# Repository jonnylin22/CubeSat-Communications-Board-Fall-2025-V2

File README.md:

# UCI CubeSat Communications Board Version 2 #

Features pinout connector to external MCU  
RX and TX status LEDs  
Organized BOM

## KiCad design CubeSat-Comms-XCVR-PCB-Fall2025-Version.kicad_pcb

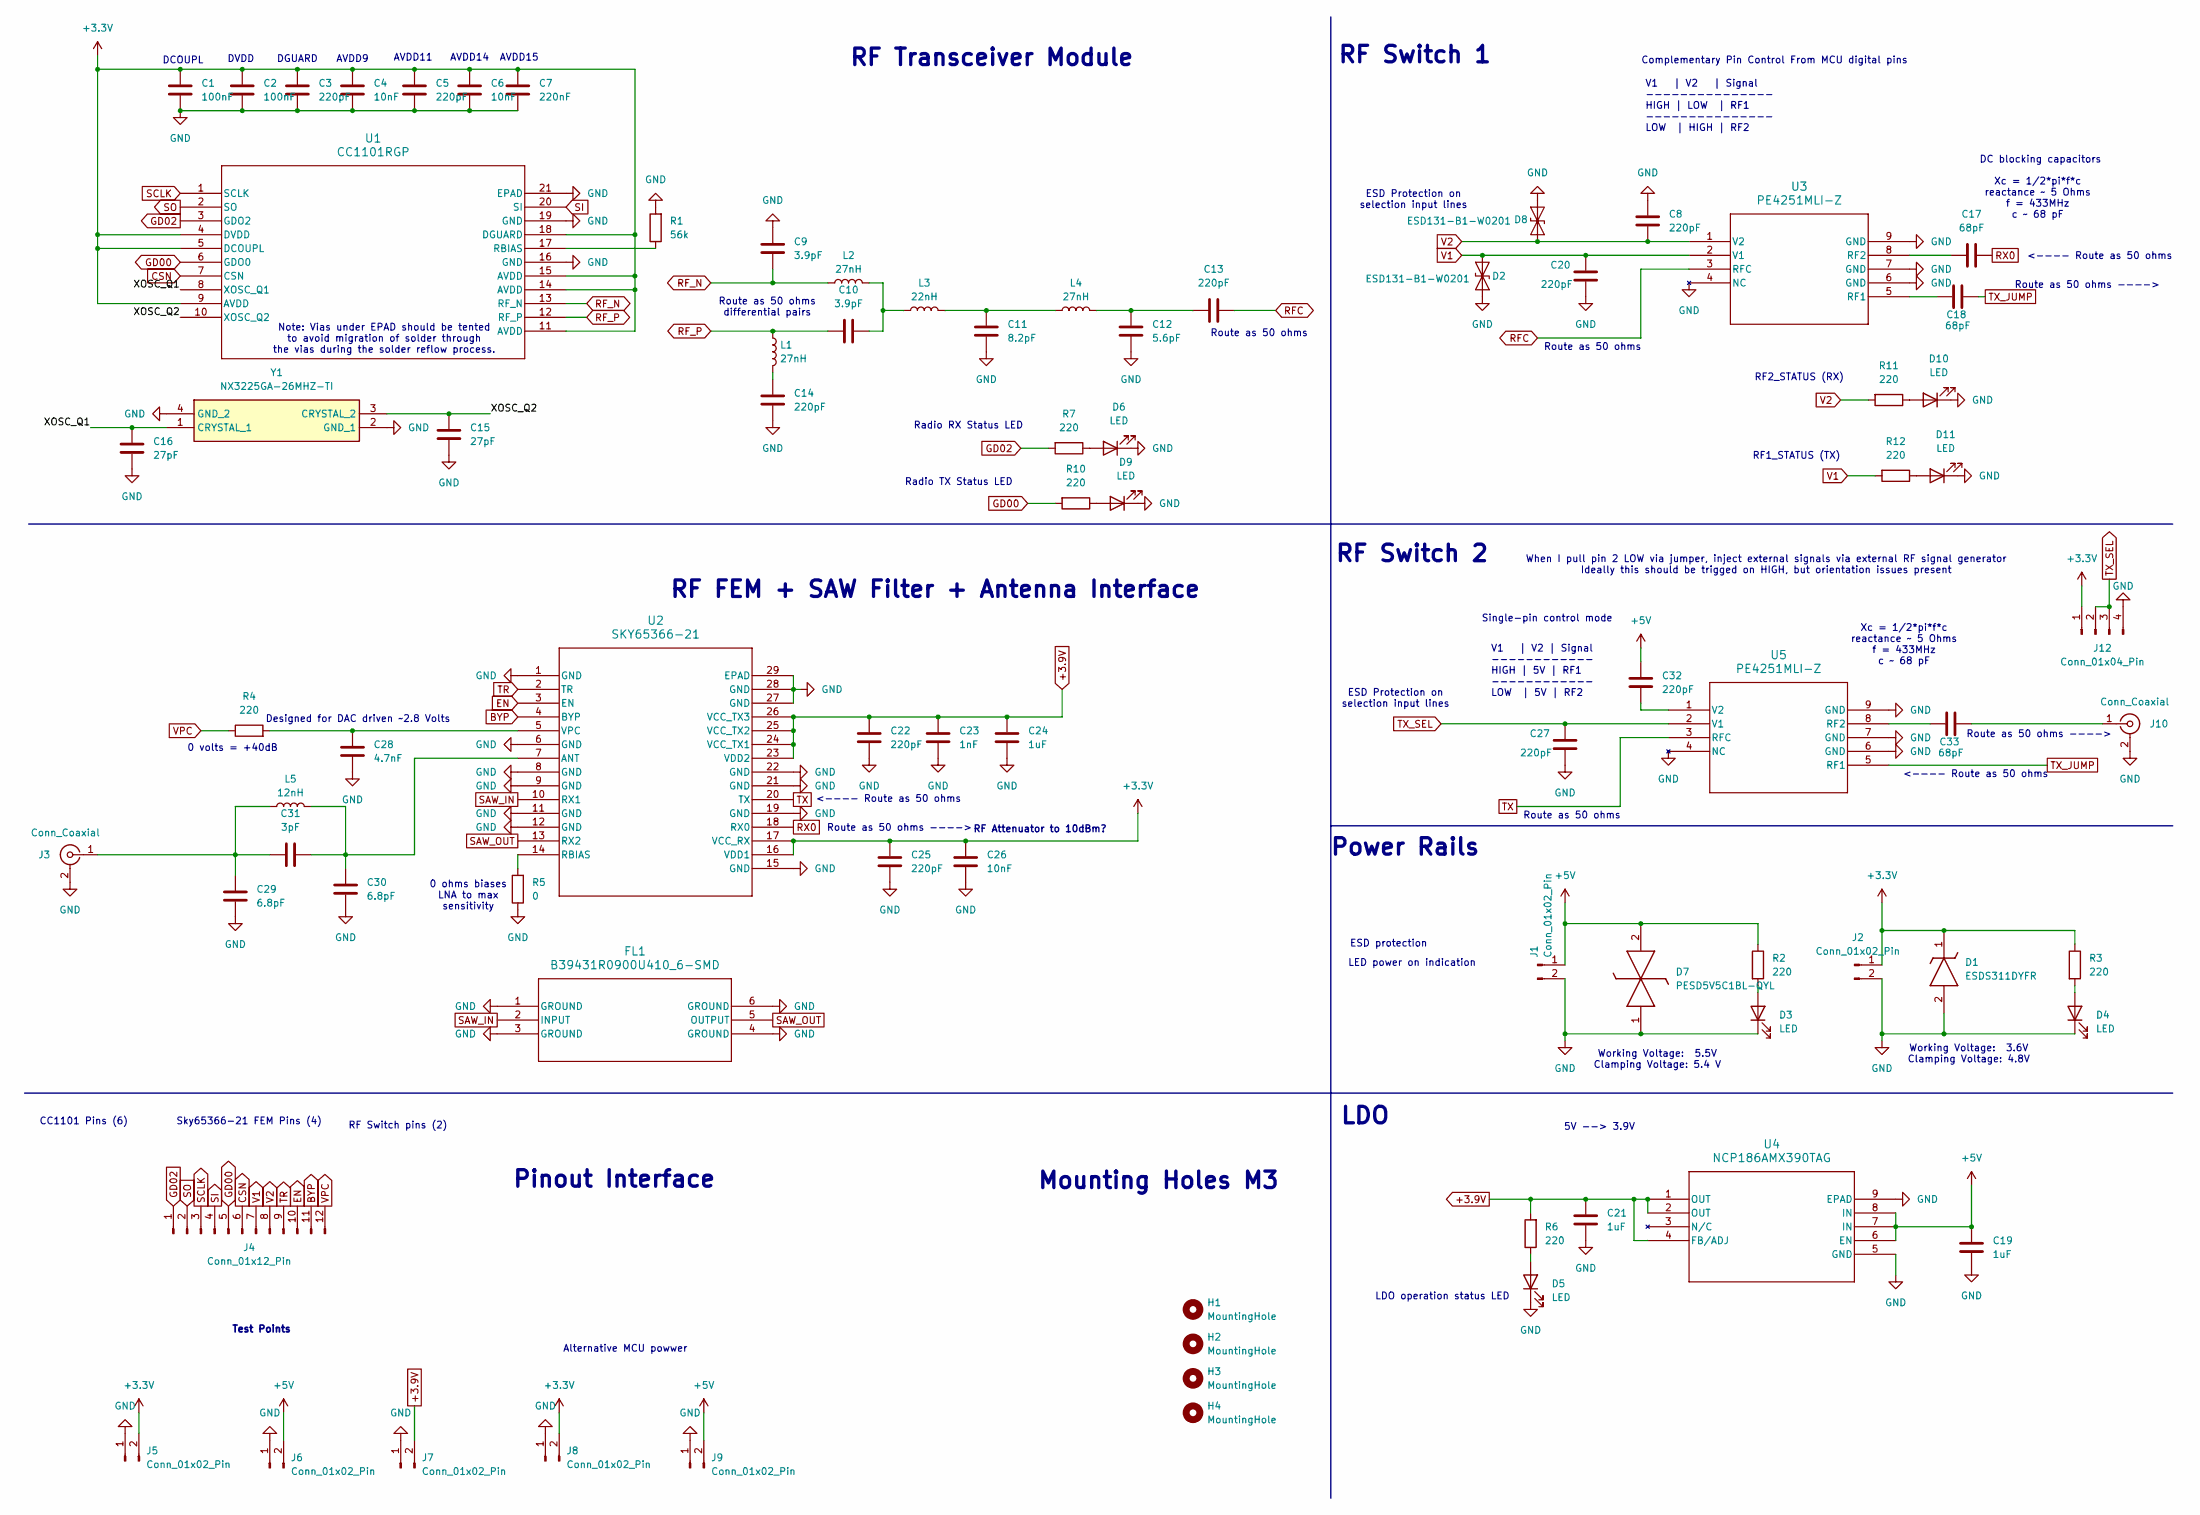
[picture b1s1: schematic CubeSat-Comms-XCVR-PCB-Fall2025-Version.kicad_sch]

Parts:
C1, C2: 100nF; G-188_MUR-L-100nF-GRM188; Manufacturer_Part_Number GRM188R72A104KA35D; LCSC Part # C77058
C3, C5, C8, C13, C14, C20, C22, C25, C27, C32: 220pF; G-188_MUR-L-100nF-GRM188; Manufacturer_Part_Number GCM1885C1H221JA16D; LCSC Part # C126556
C4, C6, C26: 10nF; G-188_MUR-L-100nF-GRM188; Manufacturer_Part_Number GRM188R72A103KA01D; LCSC Part # C162275
C7: 220nF; G-188_MUR-L-100nF-GRM188; Manufacturer_Part_Number GRM188R71E224KA88D; LCSC Part # C77051
C9, C10: 3.9pF; CAP_600S0R1AT250XT_ATC; Manufacturer_Part_Number Kyocera AVX 600S3R9BT250XT; LCSC Part # C3849659
C11: 8.2pF; G-188_MUR-L-100nF-GRM188; Manufacturer_Part_Number GQM1875C2E8R2CB12D; LCSC Part # C3874850
C12: 5.6pF; G-188_MUR-L-100nF-GRM188; Manufacturer_Part_Number GQM1875C2E5R6BB12D; LCSC Part # C2297617
C15, C16: 27pF; G-188_MUR-L-100nF-GRM188; Manufacturer_Part_Number GCM1885C2A270JA16D; LCSC Part # C909846
C17, C18, C33: 68pF; G-188_MUR-L-100nF-GRM188; Manufacturer_Part_Number GCM1885C2A680JA16D; LCSC Part # C701299
C19, C21, C24: 1uF; G-188_MUR-L-100nF-GRM188; Manufacturer_Part_Number GRT188R61H105KE13D; LCSC Part # C126631
C23: 1nF; G-188_MUR-L-100nF-GRM188; Manufacturer_Part_Number GRM1885C1H102JA01D; LCSC Part # C77026
C28: 4.7nF; G-188_MUR-L-100nF-GRM188; Manufacturer_Part_Number GCM188R72A472KA37D; LCSC Part # C426631
C29, C30: 6.8pF; G-188_MUR-L-100nF-GRM188; Manufacturer_Part_Number GCM1885C2A6R8DA16D; LCSC Part # C2212439
C31: 3pF; G-188_MUR-L-100nF-GRM188; Manufacturer_Part_Number GQM1875C2E3R0BB12D; LCSC Part # C2178931
D1: ESDS311DYFR; Manufacturer_Part_Number ESDS311DYFR; Mouser Part Number 595-ESDS311DYFR
D2, D8: ESD131-B1-W0201; Infineon_SG-WLL-2-3_0.58x0.28_P0.36mm
D3, D4, D5, D6, D9, D10, D11: LED; LED_0805_2012Metric_Pad1.15x1.40mm_HandSolder
D7: PESD5V5C1BL-QYL; PESD5V5C1BLQYL; Manufacturer_Part_Number PESD5V5C1BL-QYL; Mouser Part Number 771-PESD5V5C1BL-QYL
FL1: B39431R0900U410_6-SMD; B39431R0900U410_QUA; Manufacturer_Part_Number B39431B3710U410; LCSC Part # C2649317
H1, H2, H3, H4: MountingHole; MountingHole_3.2mm_M3_DIN965_Pad_TopBottom
J1, J2: Conn_01x02_Pin; JST_XH_B2B-XH-A_1x02_P2.50mm_Vertical
J3, J10: Conn_Coaxial; SMA_Amphenol_132134-11_Vertical; Manufacturer_Part_Number 132134; LCSC Part # C3174425
J4: Conn_01x12_Pin; PinSocket_1x12_P2.54mm_Vertical
J5, J6, J7: Conn_01x02_Pin; PinHeader_1x02_P2.54mm_Vertical
J8, J9: Conn_01x02_Pin; PinSocket_1x02_P2.54mm_Vertical
J12: Conn_01x04_Pin; PinHeader_1x04_P2.54mm_Vertical
L1, L2, L4: 27nH; INDC1005X55N; Manufacturer_Part_Number LQG15HS4N7S02D; LCSC Part # C86065
L3: 22nH; INDC1005X55N; Manufacturer_Part_Number LQG15HS22NJ02D; LCSC Part # C12670
L5: 12nH; INDC1005X55N; Manufacturer_Part_Number LQG15HS12NJ02D; LCSC Part # C77104
R1: 56k; RESC2012X60N; Manufacturer_Part_Number YAGEO RC0805FR-0756KL; LCSC Part # C137509
R2, R3, R4, R6, R7, R10, R11, R12: 220; RESC2012X60N; Manufacturer_Part_Number AC0805FR-07220RL; LCSC Part # C138270
R5: 0; CAPC1005X60
U1: CC1101RGP; RGP20_2P4X2P4
U2: SKY65366-21; SKY65366-21_SKY
U3, U5: PE4251MLI-Z; 8-MSOP_PE4251_PSM
U4: NCP186AMX390TAG; XDFN8_1P7X1P3_ONS
Y1: NX3225GA-26MHZ-TI; NX3225GA26MHZTI; Mouser Part Number 344-NX3225GA26MHZTI

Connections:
+3.3V: C1.1, C2.1, C3.1, C4.1, C5.1, C6.1, C7.1, C25.1, C26.1, D1.1 (K), J2.1, J5.2, J8.2, J12.1, R3.1, U1.4 (DVDD), U1.5 (DCOUPL), U1.9 (AVDD), U1.11 (AVDD), U1.14 (AVDD), U1.15 (AVDD), U1.18 (DGUARD), U2.16 (VDD1), U2.17 (VCC_RX)
+3.9V: C21.1, C22.1, C23.1, C24.1, J7.2, R6.2, U2.23 (VDD2), U2.24 (VCC_TX1), U2.25 (VCC_TX2), U2.26 (VCC_TX3), U4.1 (OUT), U4.2 (OUT), U4.4 (FB/ADJ)
+5V: C19.1, C32.2, D7.2 (K2), J1.1, J6.2, J9.2, R2.1, U4.6 (EN), U4.7 (IN), U4.8 (IN)
/XOSC_Q1: C16.2, U1.8 (XOSC_Q1), Y1.1 (CRYSTAL_1)
/XOSC_Q2: C15.2, U1.10 (XOSC_Q2), Y1.3 (CRYSTAL_2)
BYP: J4.11, U2.4 (BYP)
CSN: J4.6, U1.7 (CSN)
EN: J4.10, U2.3 (EN)
GD00: J4.5, R10.2, U1.6 (GDO0)
GD02: J4.1, R7.2, U1.3 (GDO2)
GND: C1.2, C2.2, C3.2, C4.2, C5.2, C6.2, C7.2, C8.2, C9.1, C11.1, C12.1, C14.1, C15.1, C16.1, C19.2, C20.1, C21.2, C22.2, C23.2, C24.2, C25.2, C26.2, C27.1, C28.2, C29.2, C30.2, D1.2 (A), D2.1 (A1), D3.1 (K), D4.1 (K), D5.1 (K), D6.1 (K), D7.1 (K1), D8.1 (A1), D9.1 (K), D10.1 (K), D11.1 (K), FL1.1 (GROUND), FL1.3 (GROUND), FL1.4 (GROUND), FL1.6 (GROUND), J1.2, J2.2, J3.2 (Ext), J5.1, J6.1, J7.1, J8.1, J9.1, J10.2 (Ext), J12.4, R1.2, R5.1, U1.16 (GND), U1.19 (GND), U1.21 (EPAD), U1.V, U2.1 (GND), U2.6 (GND), U2.8 (GND), U2.9 (GND), U2.11 (GND), U2.12 (GND), U2.15 (GND), U2.19 (GND), U2.21 (GND), U2.22 (GND), U2.27 (GND), U2.28 (GND), U2.29 (EPAD), U3.4 (NC), U3.6 (GND), U3.7 (GND), U3.9 (GND), U4.5 (GND), U4.9 (EPAD), U5.4 (NC), U5.6 (GND), U5.7 (GND), U5.9 (GND), Y1.2 (GND_1), Y1.4 (GND_2)
unnamed: C10.2, L2.2, L3.1
unnamed: C11.2, L3.2, L4.1
unnamed: C12.2, C13.2, L4.2
unnamed: C14.2, L1.2
unnamed: D3.2 (A), R2.2
unnamed: D4.2 (A), R3.2
unnamed: D5.2 (A), R6.1
unnamed: D6.2 (A), R7.1
unnamed: D9.2 (A), R10.1
unnamed: D10.2 (A), R11.1
unnamed: D11.2 (A), R12.1
unnamed: C29.1, C31.1, J3.1 (In), L5.1
unnamed: C33.1, J10.1 (In)
unnamed: R1.1, U1.17 (RBIAS)
unnamed: C30.1, C31.2, L5.2, U2.7 (ANT)
unnamed: R5.2, U2.14 (RBIAS)
unnamed: C28.1, R4.2, U2.5 (VPC)
unnamed: C18.2, U3.5 (RF1)
unnamed: C17.2, U3.8 (RF2)
unnamed: C33.2, U5.8 (RF2)
unnamed: C32.1, U5.1 (V2)
RFC: C13.1, U3.3 (RFC)
RF_N: C9.2, L2.1, U1.13 (RF_N)
RF_P: C10.1, L1.1, U1.12 (RF_P)
RX0: C17.1, U2.18 (RX0)
SAW_IN: FL1.2 (INPUT), U2.10 (RX1)
SAW_OUT: FL1.5 (OUTPUT), U2.13 (RX2)
SCLK: J4.3, U1.1 (SCLK)
SI: J4.4, U1.20 (SI)
SO: J4.2, U1.2 (SO)
TR: J4.9, U2.2 (TR)
TX: U2.20 (TX), U5.3 (RFC)
TX_JUMP: C18.1, U5.5 (RF1)
TX_SEL: C27.2, J12.2, J12.3, U5.2 (V1)
V1: C20.2, D2.2 (A2), J4.7, R12.2, U3.2 (V1)
V2: C8.1, D8.2 (A2), J4.8, R11.2, U3.1 (V2)
VPC: J4.12, R4.1

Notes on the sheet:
Single-pin control mode
RF FEM + SAW Filter + Antenna Interface
Route as 50 ohms
RF Attenuator to 10dBm?
Sky65366-21 FEM Pins (4)
When I pull pin 2 LOW via jumper, inject external signals via external RF signal generator Ideally this should be trigged on HIGH, but orientation issues present
Xc = 1/2*pi*f*c reactance ~ 5 Ohms f = 433MHz c ~ 68 pF
0 volts = +40dB
RF Switch pins (2)
ESD Protection on selection input lines
AVDD14
Test Points
Route as 50 ohms ---->
LED power on indication
Alternative MCU powwer
LDO operation status LED
DCOUPL
V1 | V2 | Signal ------------ HIGH | 5V | RF1 ------------ LOW | 5V | RF2
RF Switch 1
0 ohms biases LNA to max sensitivity
RF1_STATUS (TX)
RF Transceiver Module
Radio TX Status LED
Note: Vias under EPAD should be tented to avoid migration of solder through the vias during the solder reflow process.
Route as 50 ohms differential pairs
<---- Route as 50 ohms
Pinout Interface
DC blocking capacitors
Designed for DAC driven ~2.8 Volts
5V --> 3.9V
RF2_STATUS (RX)
DVDD
CC1101 Pins (6)
AVDD11
Working Voltage: 3.6V Clamping Voltage: 4.8V
Radio RX Status LED
Complementary Pin Control From MCU digital pins
AVDD9
RF Switch 2
AVDD15

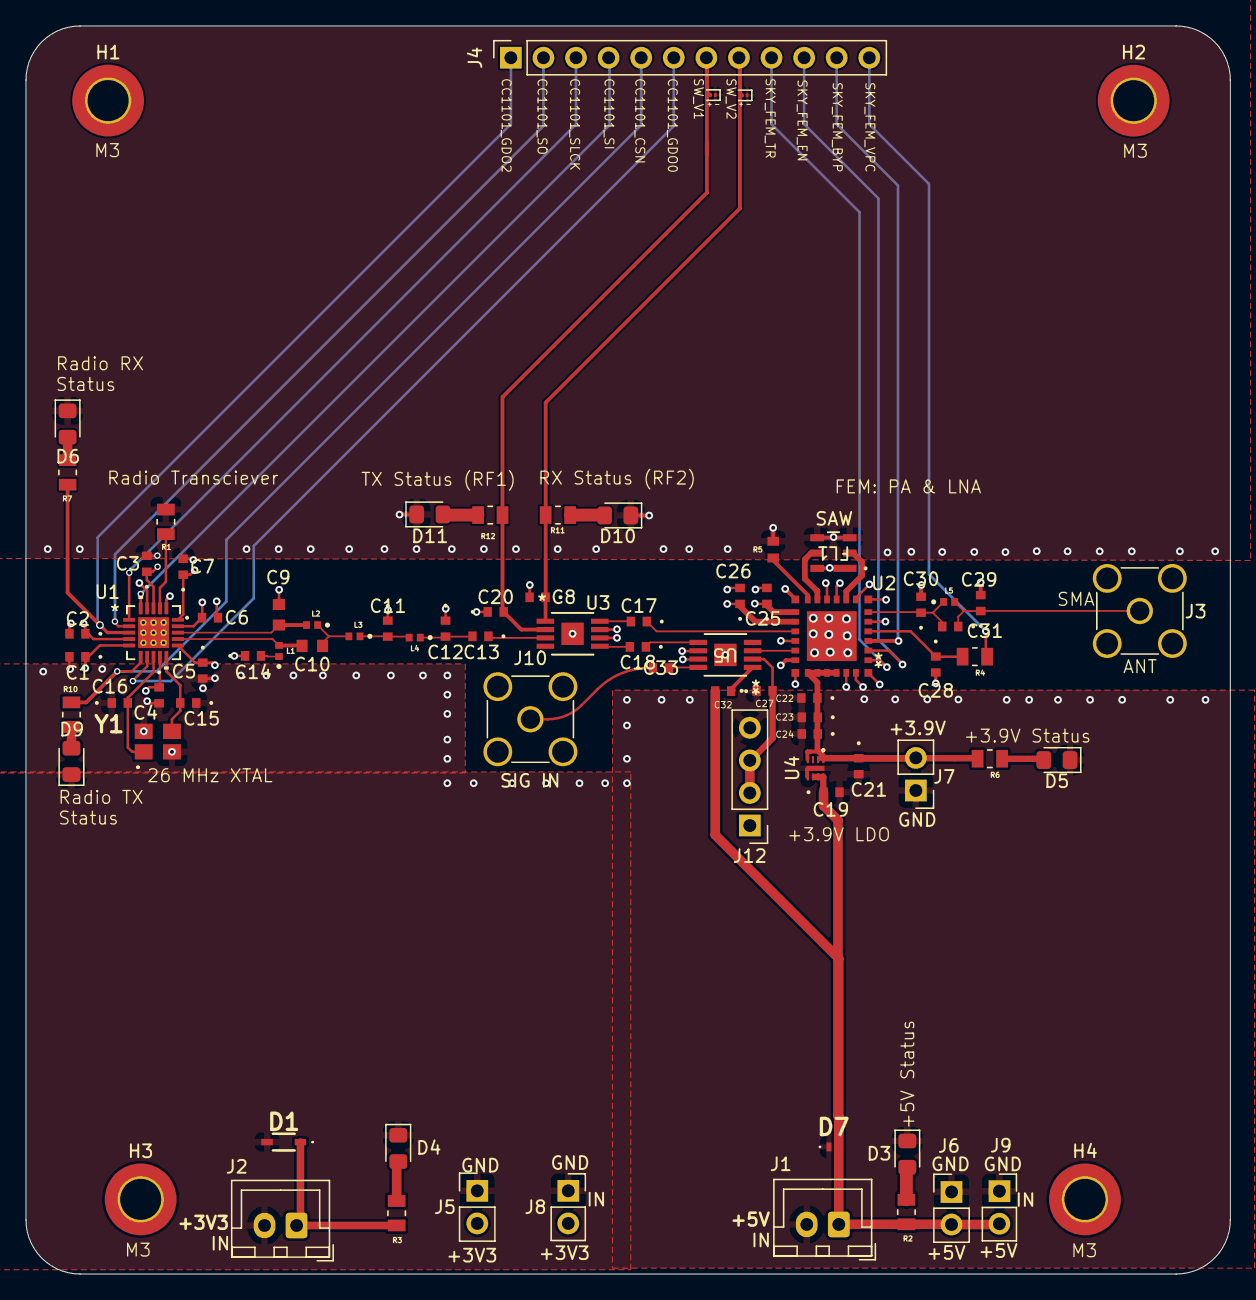
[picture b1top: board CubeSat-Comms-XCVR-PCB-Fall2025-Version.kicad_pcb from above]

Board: 4 copper layers, 93.9 x 97.3 mm, 81 parts (0 on the bottom side), 48 nets.

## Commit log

2025-11-20 CubeSat Comms PCB Fall 2025 Version 2
2025-11-20 added readme
2025-11-20 readme spaces
2025-11-28 updated mounting holes to have plated connections
2025-11-30 Add KiCad project
2025-11-30 Update KiCad project
2025-12-02 updated trace wiring
2025-12-03 edits
2025-12-03 revised TVS ESD protection diodes, added JST XH connectors for power
2025-12-03 slight edit
2025-12-04 updating vivobook
2025-12-04 pcb edits: sticking vias, trace routing...
2025-12-09 revised board clearance rules, drc, routing, placements. TODO = redundant xcvr, impedance matching
2025-12-09 editted silk screen and note on schematic about via tenting for CC1101 epad vias
2025-12-14 test points and silkscreen
2025-12-15 added external signal injecting capability
2025-12-18 empty commit
